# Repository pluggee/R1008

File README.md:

# R1008
Dual Platinum RTD Sensors
License
-------
R1008 is released under the GNU GPL v3, which you can find at <http://www.gnu.org/licenses/gpl-3.0.en.html>,
Check License.md for more details.

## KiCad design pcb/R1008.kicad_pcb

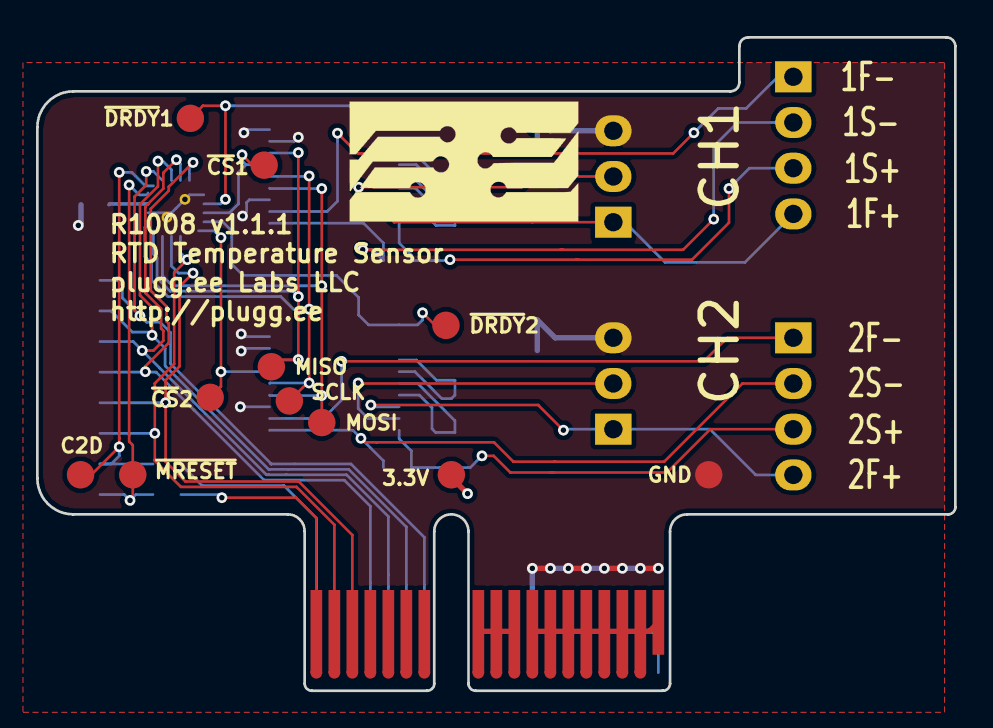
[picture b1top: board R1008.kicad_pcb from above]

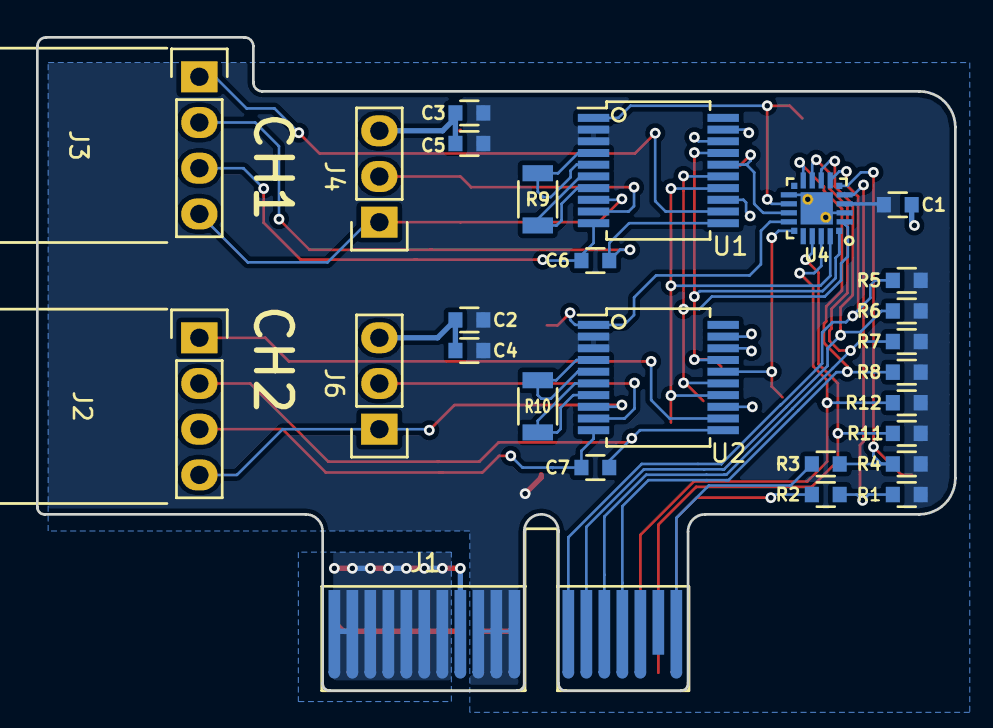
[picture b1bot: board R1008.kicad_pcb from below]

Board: 2 copper layers, 51.0 x 36.3 mm, 39 parts (27 on the bottom side), 35 nets.

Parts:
A1: ART; pluggeeLabsIcon-13X7
C1, C2, C3, C4, C5, C6, C7: CC0603KRX7R9BB104; CAPC0603
J1: PCIEXPRESS-X1
J2, J3: SOCKET254P-01X04-1725672; 70553-0038
J4, J6: CONN_01X03; CONN254P-01X03
R1, R4, R5, R6, R7, R8, R11, R12: RC0603FR-0710KL; RESC0603
R2, R3: RC0603FR-071KL; RESC0603
R9, R10: RN732BTTD4000B25; RESC1206
TP1, TP2, TP3, TP4, TP5, TP6, TP7, TP8, TP9, TP10, TP11: TestPoint; TestPoint000
U1, U2: MAX31865AAP+; SOP65P720X530X186-20
U4: EFM8BB10F8G; QFN50P300X300X75-20NT170X170

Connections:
+3V3: C1.1, C2.1, C3.1, C4.1, C5.1, J1.B9, J1.B10, J1.B11, R1.2, R4.2, R5.2, R6.2, R7.2, R8.2, R11.2, R12.2, TP1.1, U1.2, U1.3, U2.2, U2.3, U4.4
+5V: J1.A9, J1.A10, J1.A11
/C2D_CON: J1.B18, R3.2
/FORCE2_1: J4.2, U1.9
/FORCE2_2: J6.2, U2.9
/FORCE+_1: J3.4, J4.1, U1.8
/FORCE+_2: J2.4, J6.1, U2.8
/FORCE-_1: J3.1, U1.12
/FORCE-_2: J2.1, U2.12
/MISO: TP7.1, U1.17, U2.17, U4.1
/MOSI: TP9.1, U1.14, U2.14, U4.20
/R+_1: R9.1, U1.4, U1.5
/R+_2: R10.1, U2.4, U2.5
/R-_1: R9.2, U1.6, U1.7
/R-_2: R10.2, U2.6, U2.7
/RTDIN+_1: C6.1, J3.3, U1.10
/RTDIN+_2: C7.1, J2.3, U2.10
/RTDIN-_1: C6.2, J3.2, U1.11
/RTDIN-_2: C7.2, J2.2, U2.11
/SCLK: TP5.1, U1.15, U2.15, U4.2
/~CS~1: TP8.1, U1.16, U4.14
/~CS~2: TP11.1, U2.16, U4.16
/~DRDY~1: TP6.1, U1.1, U4.13
/~DRDY~2: TP10.1, U2.1, U4.15
/~MRESET~_CON: J1.A18, R2.1
C2D: R3.1, R4.1, TP3.1, U4.6
GND: C1.2, C2.2, C3.2, C4.2, C5.2, J1.B1, J1.B2, J1.B3, J1.B4, J1.B5, J1.B6, J1.B7, J1.B8, J4.3, J6.3, TP2.1, U1.13, U1.18, U1.19, U2.13, U2.18, U2.19, U4.3, U4.12, U4.21
HT: J1.A1, J1.A2, J1.A3, J1.A4, J1.A5, J1.A6, J1.A7, J1.A8
ID0: J1.B12, R5.1, U4.7
ID1: J1.B13, R6.1, U4.8
ID2: J1.B14, R7.1, U4.9
ID3: J1.B15, R8.1, U4.10
SCL: J1.A16, R12.1, U4.19
SDA: J1.A17, R11.1, U4.18
~MRESET: R1.1, R2.2, TP4.1, U4.5

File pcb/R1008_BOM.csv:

Reference;Quantity;Value;Footprint;Datasheet;Manufacturer;MPN;SKU;C;Tol;Vmax;Type;Res;Pwr
A1 ;1;ART;pluggee:pluggeeLabsIcon-13X7;
C1 C2 C3 C4 C5 C6 C7 ;7;CC0603KRX7R9BB104;Main:CAPC0603;;Yageo;CC0603KRX7R9BB104;STUFF;100 nF;±10%;50.0V;X7R;;
J1 ;1;PCIEXPRESS-X1;Main:PCIEXPRESS-X1;;Amphenol FCI;10018784-10200TLF;;;;;;;
J2 J3 ;2;SOCKET254P-01X04-1725672;Main:70553-0038;;Molex;70553-0038;STUFF;;;;;;
J4 J6 ;2;CONN_01X03;Main:CONN254P-01X03;;Amphenol FCI;68001-403HLF;STUFF;;;;;;
R1 R11 R12 R4 R5 R6 R7 R8 ;8;RC0603FR-0710KL;Main:RESC0603;;Yageo;RC0603FR-0710KL;STUFF;;±1%;;;10.0 kΩ;100 mW
R10 R9 ;2;RN732BTTD4000B25;Main:RESC1206;;KOA Speer;RN732BTTD4000B25;STUFF;;±0.1%;;;400 Ω;125 mW
R2 R3 ;2;RC0603FR-071KL;Main:RESC0603;;Yageo;RC0603FR-071KL;STUFF;;±1%;;;1.00 kΩ;100 mW
TP1 TP10 TP11 TP2 TP3 TP4 TP5 TP6 TP7 TP8 TP9 ;11;TestPoint;Main:TestPoint000;
U1 U2 ;2;MAX31865AAP+;Main:SOP65P720X530X186-20;;Maxim Integrated;MAX31865AAP+;STUFF;;;;;;
U4 ;1;EFM8BB10F2G;Main:QFN50P300X300X75-20NT170X170;;Silicon Labs;EFM8BB10F2G-A-QFN20R;STUFF;;;;;;

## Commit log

2016-12-13 first commit, added pcb project
2016-12-14 ready for release, gerbers updated
2016-12-14 re-confirmed gerbers, ready for release
2017-01-11 updated BOM
2017-02-02 added license
2017-04-18 added bootloader
2017-04-21 first firmware commit
2017-04-23 wip, ADC outputs are clean, theres a problem with FP calculations on 8bit mcu
2017-04-23 removed rtdlsb and rtdmsb from externs
2017-04-24 completely functional, got rid of casting problem that was causing weird floating point operations
2017-04-24 cleaned up code, still need to add code to measure internal die temeprature
2017-04-25 added internal temperature monitor, cleaned up, not properly documented yet
2017-04-27 added BOM, selected proper part for jumpers, added test points
2017-04-27 regenerated gerbers
2017-04-28 added to gitignore
2017-05-01 updated BOM with proper connector
2017-06-27 ready for v1.1.1 release
2017-09-02 updated firmware with 50Hz and 60Hz options
2017-09-28 added combined binary
2017-10-30 updated gitignore
2017-10-30 merged gitignore
